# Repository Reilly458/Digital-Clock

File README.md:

# Digital-Clock

## Goal: 
Design a 3D printable housing and circuitry for a wall powered digital clock. Ensure proper ventilation in the housing, to avoid component overheating, and timing accuracy minimizing any potential sources of drift. 

## Tasks: 
- [x] Circuitry for prototype
- [x] Prototype code
- [x] Arduino replica schematic and PCB layout
- [x] Main housing unit with ventilation and LCD screen mounting
- [ ] Integrate a microcontroller with more accurate timers/counters, or implement a Real Time Clock to improve accuracy and eliminate drift.
- [ ] Add PCB mounting to base of housing unit
- [ ] Design backing and power adapter mounting
- [ ] 3D print housing
- [ ] Design circuitry with a voltage regulator to handle voltage from a wall outlet
- [ ] Fix code bugs for button debouncing and reset zeroing

## Resources/Reference:
Arduino replica board https://www.instructables.com/DIY-Arduino-UNO-How-to-Make-Your-Own-Arduino-Uno-B/ 

Arduino reference schematic https://www.arduino.cc/en/uploads/Main/arduino-uno-schematic.pdf

Circuitry and code reference https://www.hackster.io/mohammadsohail0008/arduino-digital-clock-0e9c11

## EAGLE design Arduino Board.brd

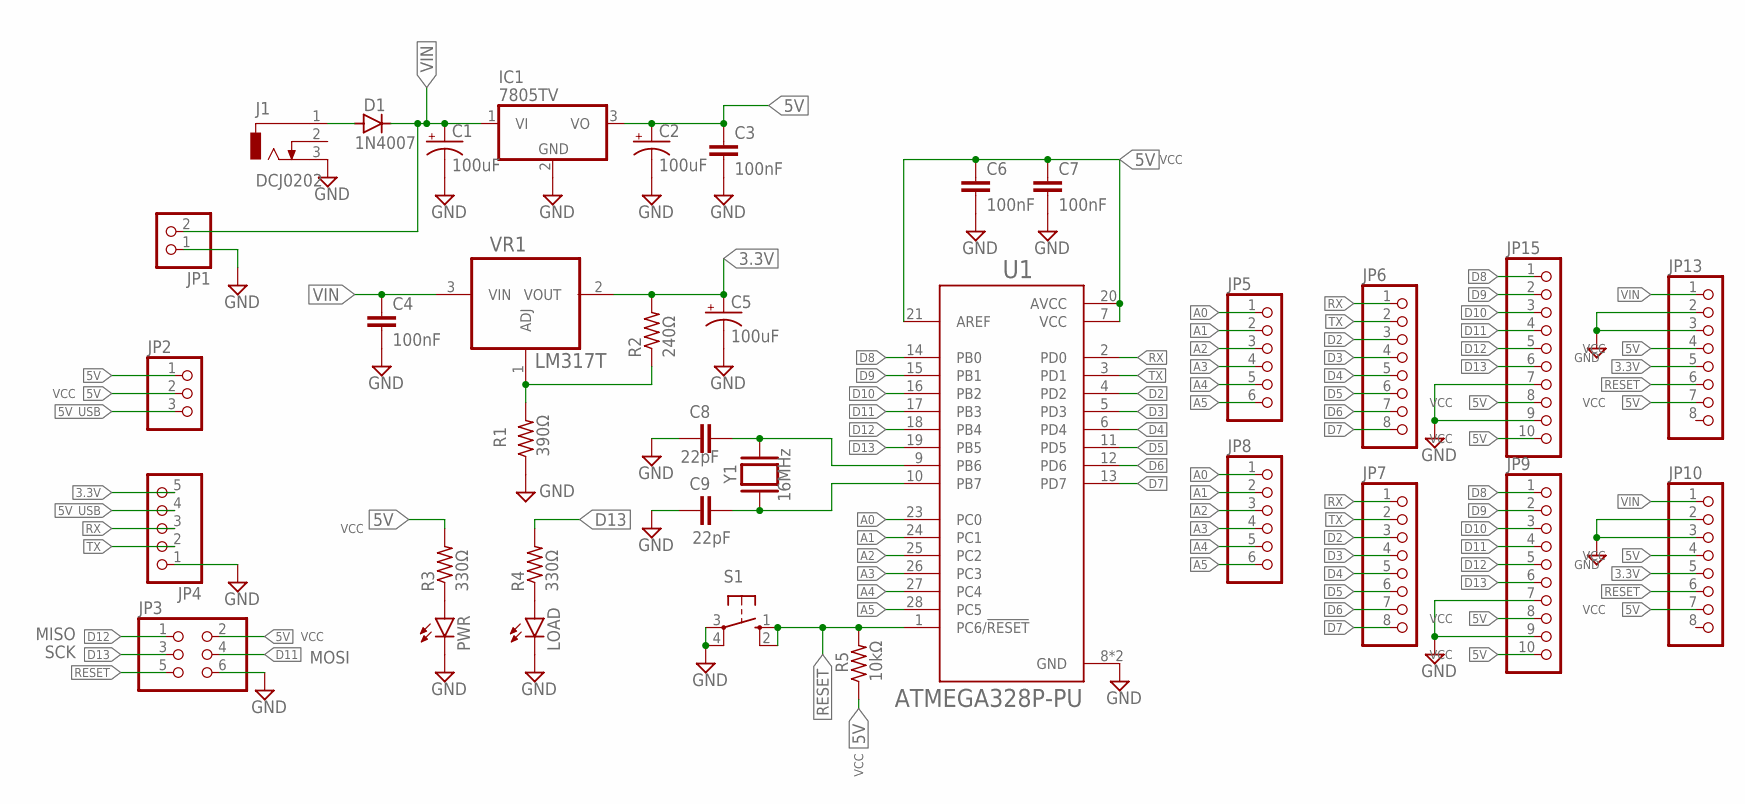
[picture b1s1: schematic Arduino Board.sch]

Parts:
C1, C2, C5: 100uF; E2,5-6
C3, C4, C6, C7: 100nF; C025-025X050
C8, C9: 22pF; C025-025X050
D1: 1N4007; DO41-10
IC1: 7805TV; TO220V
J1: DCJ0202
JP1: PINHD-1X2; 1X02
JP2: PINHD-1X3; 1X03
JP3: PINHD-2X3; 2X03
JP4: PINHD-1X5; 1X05
JP5, JP8: PINHD-1X6; 1X06
JP6, JP7, JP10, JP13: PINHD-1X8; 1X08
JP9, JP15: PINHD-1X10; 1X10
LOAD: LED3MM
PWR: LED3MM
R1: 390Ω; 0204/7
R2: 240Ω; 0204/7
R3, R4: 330Ω; 0204/7
R5: 10kΩ; 0204/7
S1: 10-XX; B3F-10XX
U1: ATMEGA328P-PU; DIP794W46P254L2967H457Q28B
VR1: LM317T; TO254P1054X470X1955-3
Y1: 16MHz; XTAL_HC49P488W46L1150T500H350

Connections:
3.3V: C5.+, JP4.5, JP10.5, JP13.5, R2.2, VR1.2 (VOUT)
5V: C2.+, C3.1, C6.1, C7.1, IC1.3 (VO), JP2.1, JP2.2, JP3.2, JP9.8, JP9.10, JP10.4, JP10.7, JP13.4, JP13.7, JP15.8, JP15.10, R3.2, R5.1, U1.7 (VCC), U1.20 (AVCC), U1.21 (AREF)
5V_USB: JP2.3, JP4.4
A0: JP5.1, JP8.1, U1.23 (PC0)
A1: JP5.2, JP8.2, U1.24 (PC1)
A2: JP5.3, JP8.3, U1.25 (PC2)
A3: JP5.4, JP8.4, U1.26 (PC3)
A4: JP5.5, JP8.5, U1.27 (PC4)
A5: JP5.6, JP8.6, U1.28 (PC5)
D2: JP6.3, JP7.3, U1.4 (PD2)
D3: JP6.4, JP7.4, U1.5 (PD3)
D4: JP6.5, JP7.5, U1.6 (PD4)
D5: JP6.6, JP7.6, U1.11 (PD5)
D6: JP6.7, JP7.7, U1.12 (PD6)
D7: JP6.8, JP7.8, U1.13 (PD7)
D8: JP9.1, JP15.1, U1.14 (PB0)
D9: JP9.2, JP15.2, U1.15 (PB1)
D10: JP9.3, JP15.3, U1.16 (PB2)
D11: JP3.4, JP9.4, JP15.4, U1.17 (PB3)
D12: JP3.1, JP9.5, JP15.5, U1.18 (PB4)
D13: JP3.3, JP9.6, JP15.6, R4.2, U1.19 (PB5)
GND: C1.-, C2.-, C3.2, C4.2, C5.-, C6.2, C7.2, C8.1, C9.1, IC1.2 (GND), J1.3, JP1.1, JP3.6, JP4.1, JP9.7, JP9.9, JP10.2, JP10.3, JP13.2, JP13.3, JP15.7, JP15.9, LOAD.K (C), PWR.K (C), R1.1, S1.3, S1.4 (P1), U1.8 (GND), U1.22 (GND)
unnamed: D1.A, J1.1
unnamed: PWR.A, R3.1
unnamed: LOAD.A, R4.1
unnamed: R1.2, R2.1, VR1.1 (ADJ)
unnamed: C8.2, U1.9 (PB6), Y1.2
unnamed: C9.2, U1.10 (PB7), Y1.1
RESET: JP3.5, JP10.6, JP13.6, R5.2, S1.1 (S), S1.2 (S1), U1.1 (PC6/!RESET)
RX: JP4.3, JP6.1, JP7.1, U1.2 (PD0)
TX: JP4.2, JP6.2, JP7.2, U1.3 (PD1)
VIN: C1.+, C4.1, D1.C, IC1.1 (VI), JP1.2, JP10.1, JP13.1, VR1.3 (VIN)

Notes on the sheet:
MISO
SCK
MOSI
VCC

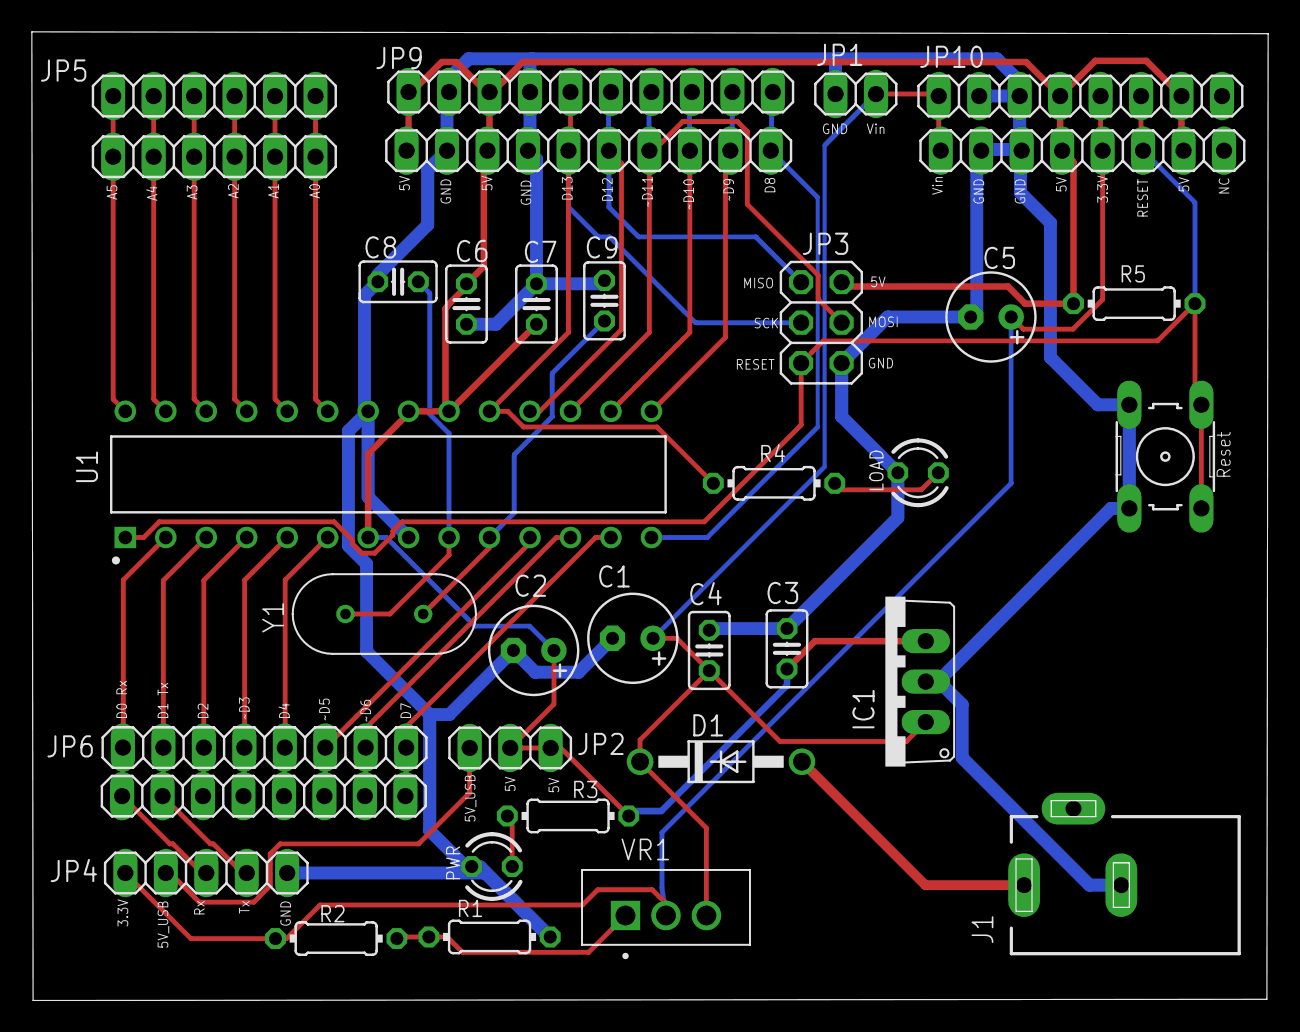
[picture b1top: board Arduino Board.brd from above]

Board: 2 copper layers, 77.6 x 60.8 mm, 35 parts (0 on the bottom side), 32 nets.

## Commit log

2025-06-03 Add files via upload
    Adding schematic and board layout pdf for arduino equivalent
2025-06-03 Update README.md
    Adding project description and progress
2025-06-03 Adding Arduino replica gerber, drill, schematic and board files
2025-06-03 Adding clock arduino code
2025-06-03 Adding solidworks housing parts
2025-06-03 Adding photo and video of clock breadboard
2025-06-03 Digital Clock housing drawing
